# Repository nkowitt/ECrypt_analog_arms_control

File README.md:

# ECrypt_analog_arms_control
Design documentation for the analog information barrier circuit and data described in Warhead Verification with Neutron Beams and an
Analog Information Barrier.

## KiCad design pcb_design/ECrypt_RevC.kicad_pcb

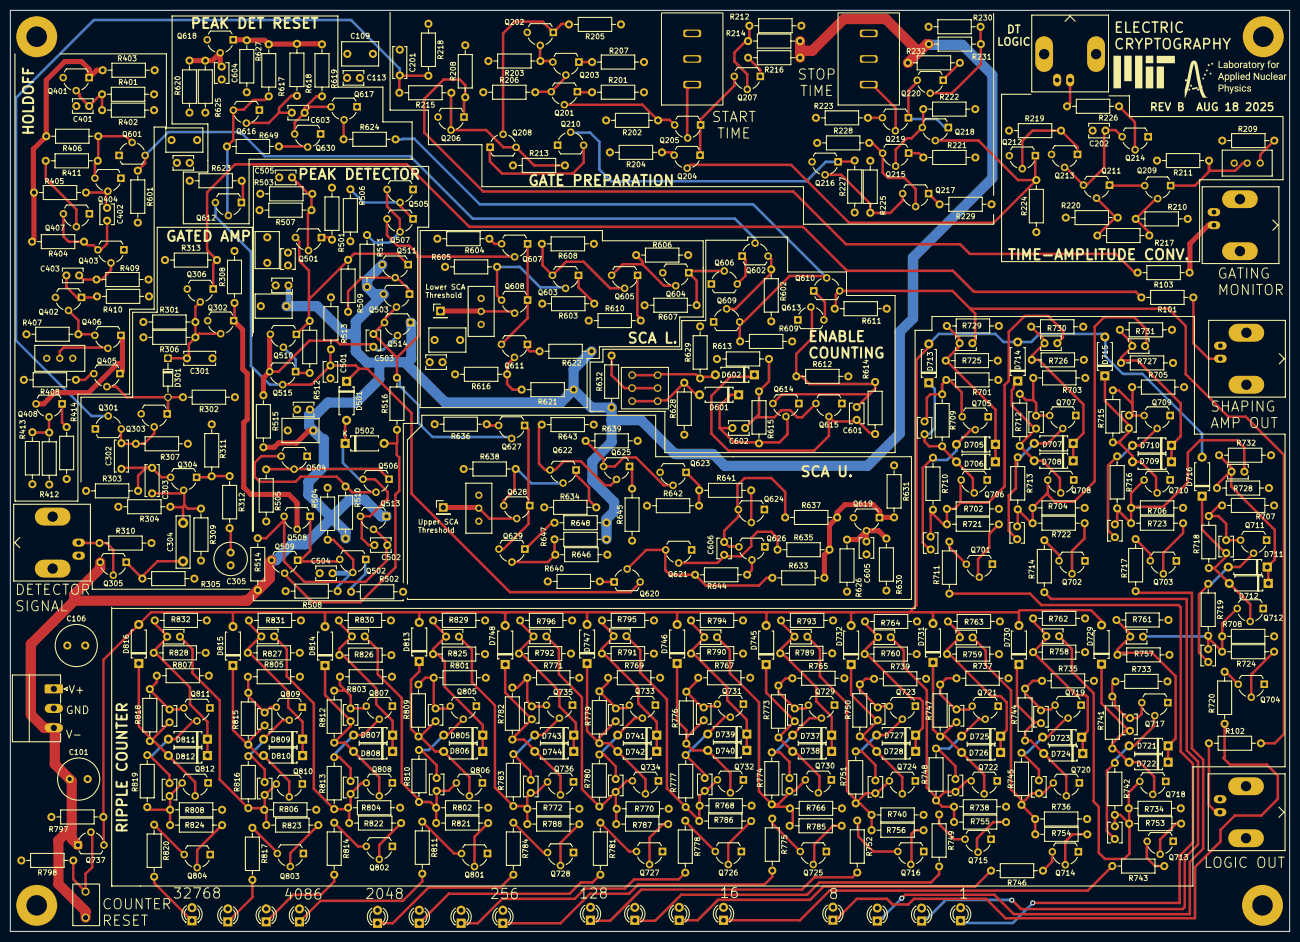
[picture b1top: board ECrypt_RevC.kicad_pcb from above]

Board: 4 copper layers, 250.0 x 180.0 mm, 556 parts (0 on the bottom side), 266 nets.

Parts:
C101, C106: 100u; C_Radial_D8.0mm_H7.0mm_P3.50mm
C102, C103, C107, C108, C109, C110: 100n; C_Rect_L7.0mm_W4.5mm_P5.00mm
C104, C105, C111, C112, C113, C114, C202, C403, C501: 1n; C_Disc_D3.8mm_W2.6mm_P2.50mm
C201: 470p; C_Disc_D6.0mm_W2.5mm_P5.00mm
C301: 100p; C_Disc_D6.0mm_W2.5mm_P5.00mm
C302: 10n; C_Disc_D6.0mm_W2.5mm_P5.00mm
C303: 22p; C_Disc_D6.0mm_W2.5mm_P5.00mm
C304: 1n; C_Rect_L10.0mm_W2.5mm_P7.50mm_MKS4
C305: 1u; C_Radial_D6.3mm_H5.0mm_P2.50mm
C401, C504, C505, C604, C605: 10n; C_Disc_D3.8mm_W2.6mm_P2.50mm
C402, C603: 2.2n; C_Disc_D3.8mm_W2.6mm_P2.50mm
C502: 22p; C_Disc_D3.8mm_W2.6mm_P2.50mm
C503: 100p; C_Disc_D3.8mm_W2.6mm_P2.50mm
C601, C602, C701, C702, C703, C704, C705, C706, C707, C708, C713, C714, C715, C716, C717, C718, C719, C720, C725, C726, C727, C728, C729, C730, C731, C732, C801, C802, C803, C804, C805, C806, C807, C808: 270p; C_Disc_D3.8mm_W2.6mm_P2.50mm
C606: 4.7n; C_Disc_D3.8mm_W2.6mm_P2.50mm
C709, C710, C711, C712, C721, C722, C723, C724, C733, C734, C735, C736, C809, C810, C811, C812: 220p; C_Disc_D3.8mm_W2.6mm_P2.50mm
D301: D; D_DO-34_SOD68_P7.62mm_Horizontal
D501, D502, D601, D602, D705, D706, D707, D708, D709, D710, D711, D712, D713, D714, D715, D716, D721, D722, D723, D724, D725, D726, D727, D728, D729, D730, D731, D732, D737, D738, D739, D740, D741, D742, D743, D744, D745, D746, D747, D748, D805, D806, D807, D808, D809, D810, D811, D812, D813, D814, D815, D816: D; D_A-405_P7.62mm_Horizontal
D701, D702, D703, D704, D717, D718, D719, D720, D733, D734, D735, D736, D801, D802, D803, D804: LED; LED_D3.0mm
H101, H102, H103, H104: MountingHole_Pad; MountingHole_4mm_Pad
J101: Conn_01x03_Pin; PhoenixContact_MC_1,5_3-G-3.81_1x03_P3.81mm_Horizontal
J102, J103, J104, J105, J106: Conn_Coaxial; BNC_Amphenol_B6252HB-NPP3G-50_Horizontal
Q201, Q206, Q209, Q211, Q213, Q215, Q303, Q305, Q501, Q502, Q503, Q504, Q505, Q506, Q507, Q508, Q509, Q510, Q511, Q515, Q603, Q622: 2N3906; TO-92L_Wide
Q202, Q203, Q204, Q205, Q207, Q212, Q214, Q216, Q217, Q218, Q219, Q220, Q302, Q304, Q306, Q401, Q402, Q403, Q404, Q405, Q406, Q407, Q408, Q513, Q514, Q604, Q605, Q607, Q608, Q611, Q614, Q615, Q616, Q617, Q618, Q619, Q621, Q623, Q624, Q625, Q626, Q627, Q628, Q629, Q630, Q701, Q702, Q703, Q704, Q705, Q706, Q707, Q708, Q709, Q710, Q711, Q712, Q713, Q714, Q715, Q716, Q717, Q718, Q719, Q720, Q721, Q722, Q723, Q724, Q725, Q726, Q727, Q728, Q729, Q730, Q731, Q732, Q733, Q734, Q735, Q736, Q801, Q802, Q803, Q804, Q805, Q806, Q807, Q808, Q809, Q810, Q811, Q812: 2N3904; TO-92L_Wide
Q208, Q210, Q301, Q601, Q602, Q606, Q609, Q610, Q612, Q613, Q620, Q737: 2N7000; TO-92L_Wide
R101, R102, R103, R310, R505, R506: 50; R_Axial_DIN0207_L6.3mm_D2.5mm_P10.16mm_Horizontal
R201, R202, R204, R205, R207, R208, R209, R211, R213, R215, R216, R218, R221, R222, R223, R226, R227, R229, R232, R303, R401, R402, R403, R404, R406, R409, R414, R501, R502, R503, R504, R601, R602, R603, R607, R609, R610, R611, R612, R613, R617, R618, R619, R620, R622, R624, R625, R627, R633, R634, R637, R642, R645, R648, R701, R702, R703, R704, R705, R706, R707, R708, R711, R714, R717, R720, R733, R734, R735, R736, R737, R738, R739, R740, R743, R746, R749, R752, R765, R766, R767, R768, R769, R770, R771, R772, R775, R778, R781, R784, R801, R802, R803, R804, R805, R806, R807, R808, R811, R814, R817, R820: 1k; R_Axial_DIN0207_L6.3mm_D2.5mm_P10.16mm_Horizontal
R203, R225, R606, R608, R639, R643: 15k; R_Axial_DIN0207_L6.3mm_D2.5mm_P10.16mm_Horizontal
R206, R228: 5k; R_Axial_DIN0207_L6.3mm_D2.5mm_P10.16mm_Horizontal
R210, R311: 100; R_Axial_DIN0207_L6.3mm_D2.5mm_P10.16mm_Horizontal
R212, R219, R224, R230, R305, R307, R412, R604, R605, R616, R628, R629, R632, R635, R636, R638, R641, R646, R725, R726, R727, R728, R729, R730, R731, R732, R757, R758, R759, R760, R761, R762, R763, R764, R789, R790, R791, R792, R793, R794, R795, R796, R797, R798, R825, R826, R827, R828, R829, R830, R831, R832: 10k; R_Axial_DIN0207_L6.3mm_D2.5mm_P10.16mm_Horizontal
R214, R231, R413, R621, R647: 900; R_Axial_DIN0207_L6.3mm_D2.5mm_P10.16mm_Horizontal
R217: 75; R_Axial_DIN0207_L6.3mm_D2.5mm_P10.16mm_Horizontal
R220: 910; R_Axial_DIN0207_L6.3mm_D2.5mm_P10.16mm_Horizontal
R301: 2Meg; R_Axial_DIN0207_L6.3mm_D2.5mm_P10.16mm_Horizontal
R302: 1.5k; R_Axial_DIN0207_L6.3mm_D2.5mm_P10.16mm_Horizontal
R304: 3.9k; R_Axial_DIN0207_L6.3mm_D2.5mm_P10.16mm_Horizontal
R306, R614, R615, R709, R710, R712, R713, R715, R716, R718, R719, R741, R742, R744, R745, R747, R748, R750, R751, R773, R774, R776, R777, R779, R780, R782, R783, R809, R810, R812, R813, R815, R816, R818, R819: 100k; R_Axial_DIN0207_L6.3mm_D2.5mm_P10.16mm_Horizontal
R308, R313, R721, R722, R723, R724, R753, R754, R755, R756, R785, R786, R787, R788, R821, R822, R823, R824: 40k; R_Axial_DIN0207_L6.3mm_D2.5mm_P10.16mm_Horizontal
R309: 600; R_Axial_DIN0207_L6.3mm_D2.5mm_P10.16mm_Horizontal
R312: 10; R_Axial_DIN0207_L6.3mm_D2.5mm_P10.16mm_Horizontal
R405, R407, R408, R626, R630, R631: 5.6k; R_Axial_DIN0207_L6.3mm_D2.5mm_P10.16mm_Horizontal
R410, R514, R515: 2.2k; R_Axial_DIN0207_L6.3mm_D2.5mm_P10.16mm_Horizontal
R411, R649: 20k; R_Axial_DIN0207_L6.3mm_D2.5mm_P10.16mm_Horizontal
R507, R508: 11k; R_Axial_DIN0207_L6.3mm_D2.5mm_P10.16mm_Horizontal
R509, R510, R511, R512, R516, R644: 22k; R_Axial_DIN0207_L6.3mm_D2.5mm_P10.16mm_Horizontal
R513: 1Meg; R_Axial_DIN0207_L6.3mm_D2.5mm_P10.16mm_Horizontal
R623, R640: 20; R_Axial_DIN0207_L6.3mm_D2.5mm_P10.16mm_Horizontal
RV201, RV203: R_Potentiometer; Bourns 3590s
RV202, RV401, RV601, RV602: R_Potentiometer_Trim; Potentiometer_Bourns_3296W_Vertical
SW601: SW_Push_DPDT; SW_CK_JS202011CQN_DPDT_Straight
SW701: SW_SPST; SW_DIP_SPSTx01_Piano_10.8x4.1mm_W7.62mm_P2.54mm
TP601: TestPoint; PinHeader_1x01_P2.54mm_Vertical
Upper threshold: TestPoint; PinHeader_1x01_P2.54mm_Vertical

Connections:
+VDC: C106.1, C107.1, C108.1, C109.1, C110.1, C111.1, C112.1, C113.1, C114.1, D701.2 (A), D702.2 (A), D703.2 (A), D704.2 (A), D717.2 (A), D718.2 (A), D719.2 (A), D720.2 (A), D733.2 (A), D734.2 (A), D735.2 (A), D736.2 (A), D801.2 (A), D802.2 (A), D803.2 (A), D804.2 (A), J101.1, Q202.3 (C), Q212.3 (C), Q216.3 (C), Q302.3 (C), Q306.3 (C), Q401.3 (C), Q402.3 (C), Q504.1 (E), Q505.1 (E), Q604.3 (C), Q618.3 (C), Q619.3 (C), Q623.3 (C), R201.2, R202.2, R203.2, R204.2, R208.2, R209.2, R210.2, R211.2, R212.2, R213.1, R219.2, R221.2, R222.2, R223.2, R225.2, R230.2, R301.1, R302.1, R303.1, R304.1, R305.1, R401.2, R407.2, R408.2, R412.2, R501.1, R502.1, R503.1, R504.1, R505.1, R506.1, R601.2, R602.2, R603.2, R604.2, R605.2, R606.2, R609.2, R611.2, R612.2, R613.2, R616.2, R620.2, R626.2, R628.1, R629.2, R634.2, R636.2, R638.2, R639.2, R646.2, R701.2, R702.2, R703.2, R704.2, R705.2, R706.2, R707.2, R708.2, R725.2, R726.2, R727.2, R728.2, R733.2, R734.2, R735.2, R736.2, R737.2, R738.2, R739.2, R740.2, R757.2, R758.2, R759.2, R760.2, R765.2, R766.2, R767.2, R768.2, R769.2, R770.2, R771.2, R772.2, R789.2, R790.2, R791.2, R792.2, R797.2, R798.2, R801.2, R802.2, R803.2, R804.2, R805.2, R806.2, R807.2, R808.2, R825.2, R826.2, R827.2, R828.2, RV201.1, RV203.1, RV401.1, RV601.1, RV602.1
-VDC: C101.1, C102.1, C103.1, C104.1, C105.1, J101.3, Q305.3 (C), Q503.3 (C), Q509.3 (C), Q511.3 (C), Q513.1 (E), Q514.1 (E), Q737.1 (S), R214.1, R216.1, R231.1, R232.1, R510.2, R511.2, R514.2, R515.2, R621.1, R622.1, R632.1, R647.1, R648.1, SW701.1 (A)
DT_Reset: J103.1 (In), R226.1
Detector Signal: J105.1 (In), Q305.2 (B), R310.1
GND_ref: C101.2, C102.2, C103.2, C104.2, C105.2, C106.2, C107.2, C108.2, C109.2, C110.2, C111.2, C112.2, C113.2, C114.2, C201.1, C202.2, C301.1, C305.1, C401.2, C501.2, C504.2, C505.2, C604.2, C605.2, H101.1, H102.1, H103.1, H104.1, J101.2, J102.2 (Ext), J103.2 (Ext), J104.2 (Ext), J105.2 (Ext), J106.2 (Ext), Q206.3 (C), Q210.1 (S), Q213.3 (C), Q214.1 (E), Q301.1 (S), Q303.3 (C), Q403.1 (E), Q404.1 (E), Q407.1 (E), Q601.1 (S), Q606.1 (S), Q609.1 (S), Q613.1 (S), Q614.1 (E), Q615.1 (E), Q616.1 (E), Q617.1 (E), Q621.1 (E), Q624.1 (E), Q626.1 (E), Q630.1 (E), Q701.1 (E), Q702.1 (E), Q703.1 (E), Q704.1 (E), Q705.1 (E), Q706.1 (E), Q707.1 (E), Q708.1 (E), Q709.1 (E), Q710.1 (E), Q711.1 (E), Q712.1 (E), Q713.1 (E), Q714.1 (E), Q715.1 (E), Q716.1 (E), Q717.1 (E), Q718.1 (E), Q719.1 (E), Q720.1 (E), Q721.1 (E), Q722.1 (E), Q723.1 (E), Q724.1 (E), Q725.1 (E), Q726.1 (E), Q727.1 (E), Q728.1 (E), Q729.1 (E), Q730.1 (E), Q731.1 (E), Q732.1 (E), Q733.1 (E), Q734.1 (E), Q735.1 (E), Q736.1 (E), Q801.1 (E), Q802.1 (E), Q803.1 (E), Q804.1 (E), Q805.1 (E), Q806.1 (E), Q807.1 (E), Q808.1 (E), Q809.1 (E), Q810.1 (E), Q811.1 (E), Q812.1 (E), R205.1, R206.1, R207.1, R218.1, R220.1, R224.1, R227.1, R228.1, R229.1, R306.2, R307.2, R308.2, R309.2, R310.2, R311.2, R313.1, R402.1, R403.1, R409.1, R410.1, R413.1, R414.1, R507.2, R508.2, R513.2, R607.1, R608.1, R610.1, R623.1, R625.1, R627.1, R630.1, R631.1, R640.1, R642.1, R643.1, R645.1, R729.1, R730.1, R731.1, R732.1, R761.1, R762.1, R763.1, R764.1, R793.1, R794.1, R795.1, R796.1, R829.1, R830.1, R831.1, R832.1, RV201.3, RV203.3, RV401.3, RV601.3, RV602.3
Gating Monitor: Q206.1 (E), R103.2, R208.1
Gating Signal: C201.2, Q301.2 (G), R215.2, R218.2
Holdoff: Q404.3 (C), Q601.2 (G), R406.1, R411.1
unnamed: C305.2, R312.2
unnamed: C301.2, D301.1 (K), Q302.2 (B), Q306.2 (B), R301.2, R306.1
unnamed: C502.1, D501.2 (A), D502.1 (K), Q506.3 (C), Q513.3 (C)
unnamed: D502.2 (A), Q509.2 (B), R516.1
unnamed: D601.2 (A), R628.2, SW601.1 (A), SW601.4 (A)
unnamed: C602.2, D601.1 (K), Q614.2 (B), R615.1
unnamed: D602.2 (A), R629.1, SW601.3 (C), SW601.6 (C)
unnamed: C601.1, D602.1 (K), Q615.2 (B), R614.2
unnamed: D701.1 (K), R711.2
unnamed: D702.1 (K), R714.2
unnamed: D703.1 (K), R717.2
unnamed: D704.1 (K), R720.2
unnamed: C702.2, D705.2 (A), Q705.2 (B), R710.1
unnamed: C709.2, D705.1 (K), D706.1 (K), R725.1, R729.2
unnamed: C701.1, D706.2 (A), D713.1 (K), Q706.2 (B), R709.2
unnamed: C704.2, D707.2 (A), Q707.2 (B), R713.1
unnamed: C710.2, D707.1 (K), D708.1 (K), R726.1, R730.2
unnamed: C703.1, D708.2 (A), D714.1 (K), Q708.2 (B), R712.2
unnamed: C706.2, D709.2 (A), Q709.2 (B), R716.1
unnamed: C711.2, D709.1 (K), D710.1 (K), R727.1, R731.2
unnamed: C705.1, D710.2 (A), D715.1 (K), Q710.2 (B), R715.2
unnamed: C708.2, D711.2 (A), Q711.2 (B), R719.1
unnamed: C712.2, D711.1 (K), D712.1 (K), R728.1, R732.2
unnamed: C707.1, D712.2 (A), D716.1 (K), Q712.2 (B), R718.2
unnamed: D717.1 (K), R743.2
unnamed: D718.1 (K), R746.2
unnamed: D719.1 (K), R749.2
unnamed: D720.1 (K), R752.2
unnamed: C714.2, D721.2 (A), Q717.2 (B), R742.1
unnamed: C721.2, D721.1 (K), D722.1 (K), R757.1, R761.2
unnamed: C713.1, D722.2 (A), D729.1 (K), Q718.2 (B), R741.2
unnamed: C716.2, D723.2 (A), Q719.2 (B), R745.1
unnamed: C722.2, D723.1 (K), D724.1 (K), R758.1, R762.2
unnamed: C715.1, D724.2 (A), D730.1 (K), Q720.2 (B), R744.2
unnamed: C718.2, D725.2 (A), Q721.2 (B), R748.1
unnamed: C723.2, D725.1 (K), D726.1 (K), R759.1, R763.2
unnamed: C717.1, D726.2 (A), D731.1 (K), Q722.2 (B), R747.2
unnamed: C720.2, D727.2 (A), Q723.2 (B), R751.1
unnamed: C724.2, D727.1 (K), D728.1 (K), R760.1, R764.2
unnamed: C719.1, D728.2 (A), D732.1 (K), Q724.2 (B), R750.2
unnamed: D733.1 (K), R775.2
unnamed: D734.1 (K), R778.2
unnamed: D735.1 (K), R781.2
unnamed: D736.1 (K), R784.2
unnamed: C726.2, D737.2 (A), Q729.2 (B), R774.1
unnamed: C733.2, D737.1 (K), D738.1 (K), R789.1, R793.2
unnamed: C725.1, D738.2 (A), D745.1 (K), Q730.2 (B), R773.2
unnamed: C728.2, D739.2 (A), Q731.2 (B), R777.1
unnamed: C734.2, D739.1 (K), D740.1 (K), R790.1, R794.2
unnamed: C727.1, D740.2 (A), D746.1 (K), Q732.2 (B), R776.2
unnamed: C730.2, D741.2 (A), Q733.2 (B), R780.1
unnamed: C735.2, D741.1 (K), D742.1 (K), R791.1, R795.2
unnamed: C729.1, D742.2 (A), D747.1 (K), Q734.2 (B), R779.2
unnamed: C732.2, D743.2 (A), Q735.2 (B), R783.1
unnamed: C736.2, D743.1 (K), D744.1 (K), R792.1, R796.2
unnamed: C731.1, D744.2 (A), D748.1 (K), Q736.2 (B), R782.2
unnamed: D801.1 (K), R811.2
unnamed: D802.1 (K), R814.2
unnamed: D803.1 (K), R817.2
unnamed: D804.1 (K), R820.2
unnamed: C802.2, D805.2 (A), Q805.2 (B), R810.1
unnamed: C809.2, D805.1 (K), D806.1 (K), R825.1, R829.2
unnamed: C801.1, D806.2 (A), D813.1 (K), Q806.2 (B), R809.2
unnamed: C804.2, D807.2 (A), Q807.2 (B), R813.1
unnamed: C810.2, D807.1 (K), D808.1 (K), R826.1, R830.2
unnamed: C803.1, D808.2 (A), D814.1 (K), Q808.2 (B), R812.2
unnamed: C806.2, D809.2 (A), Q809.2 (B), R816.1
unnamed: C811.2, D809.1 (K), D810.1 (K), R827.1, R831.2
unnamed: C805.1, D810.2 (A), D815.1 (K), Q810.2 (B), R815.2
unnamed: C808.2, D811.2 (A), Q811.2 (B), R819.1
unnamed: C812.2, D811.1 (K), D812.1 (K), R828.1, R832.2
unnamed: C807.1, D812.2 (A), D816.1 (K), Q812.2 (B), R818.2
unnamed: J102.1 (In), R101.1
unnamed: J104.1 (In), R102.1
unnamed: J106.1 (In), R103.1
unnamed: Q201.2 (B), Q205.3 (C), R202.1
unnamed: Q201.3 (C), Q203.2 (B), R206.2
unnamed: Q201.1 (E), R201.1
unnamed: Q202.2 (B), Q203.3 (C), R203.1
unnamed: Q202.1 (E), Q208.2 (G), R205.2
unnamed: Q203.1 (E), R207.2
unnamed: Q204.2 (B), Q212.1 (E), Q218.2 (B), R224.2
unnamed: Q204.3 (C), R204.1
unnamed: Q204.1 (E), Q205.1 (E), Q207.3 (C)
unnamed: Q205.2 (B), RV201.2
unnamed: Q206.2 (B), Q208.3 (D), R213.2, R215.1
unnamed: Q207.2 (B), R212.1, R214.2
unnamed: Q207.1 (E), R216.2
unnamed: Q208.1 (S), Q210.3 (D)
unnamed: Q209.2 (B), R210.1, R217.2
unnamed: Q209.3 (C), Q211.1 (E)
unnamed: Q209.1 (E), R211.1, RV202.2
unnamed: Q210.2 (G), Q216.1 (E), R227.2
unnamed: Q211.2 (B), R217.1, R220.2
unnamed: C202.1, Q211.3 (C), Q213.2 (B), Q214.3 (C)
unnamed: Q212.2 (B), Q213.1 (E), R219.1
unnamed: Q214.2 (B), R226.2
unnamed: Q215.2 (B), Q218.3 (C), R222.1
unnamed: Q215.3 (C), Q217.2 (B), R228.2
unnamed: Q215.1 (E), R221.1
unnamed: Q216.2 (B), Q217.3 (C), R225.1
unnamed: Q217.1 (E), R229.2
unnamed: Q218.1 (E), Q219.1 (E), Q220.3 (C)
unnamed: Q219.2 (B), RV203.2
unnamed: Q219.3 (C), R223.1
unnamed: Q220.2 (B), R230.1, R231.2
unnamed: Q220.1 (E), R232.2
unnamed: C302.2, Q301.3 (D), Q303.2 (B), R307.1
unnamed: C303.1, C304.2, Q304.2 (B), R304.2, R309.1
unnamed: C302.1, C303.2, Q304.3 (C), R303.2
unnamed: Q304.1 (E), R311.1, R312.1
unnamed: C304.1, Q305.1 (E), R305.2
unnamed: C401.1, Q401.2 (B), R401.1, R402.2
unnamed: Q401.1 (E), R403.2, R404.2, R405.2, R406.2
unnamed: Q402.2 (B), Q406.3 (C), R407.1
unnamed: C403.2, Q402.1 (E), R410.2
unnamed: C403.1, Q403.2 (B), R409.2
unnamed: C402.2, Q403.3 (C), Q407.3 (C), R404.1
unnamed: C402.1, Q404.2 (B), R405.1
unnamed: Q405.3 (C), R408.1
unnamed: Q405.1 (E), Q406.1 (E), Q408.3 (C)
unnamed: Q406.2 (B), RV401.2
unnamed: Q407.2 (B), R411.2
unnamed: Q408.2 (B), R412.1, R413.2
unnamed: Q408.1 (E), R414.2
unnamed: C505.1, Q501.2 (B), R503.2, R507.1
unnamed: Q501.3 (C), Q510.1 (E), Q511.1 (E), R509.1, R512.1
unnamed: Q501.1 (E), R501.2
unnamed: C504.1, Q502.2 (B), R504.2, R508.1
unnamed: Q502.3 (C), Q508.1 (E), Q509.1 (E)
unnamed: Q502.1 (E), R502.2
unnamed: Q503.1 (E), Q511.2 (B), R509.2
unnamed: Q504.2 (B), Q506.1 (E), R505.2
unnamed: Q504.3 (C), Q506.2 (B), R510.1
unnamed: Q505.2 (B), Q507.1 (E), R506.2
unnamed: Q505.3 (C), Q507.2 (B), R511.1
unnamed: C502.2, Q508.3 (C), Q513.2 (B), R514.1
unnamed: Q510.2 (B), Q515.1 (E), R512.2
unnamed: C503.2, Q510.3 (C), Q514.2 (B), Q515.3 (C), R515.1
unnamed: Q601.3 (D), Q602.2 (G), R601.1
unnamed: Q602.3 (D), Q609.2 (G), R602.1
unnamed: Q602.1 (S), Q606.3 (D)
unnamed: Q603.2 (B), Q608.3 (C), R605.1
unnamed: Q603.3 (C), Q605.2 (B), R608.2
unnamed: Q603.1 (E), R603.1
unnamed: Q604.2 (B), Q605.3 (C), R606.1
unnamed: Q604.1 (E), Q606.2 (G), R607.2
unnamed: Q605.1 (E), R610.2
unnamed: Q607.3 (C), R604.1
unnamed: Q607.1 (E), Q608.1 (E), Q611.3 (C)
unnamed: Q608.2 (B), RV601.2, TP601.1
unnamed: Q609.3 (D), Q610.2 (G), R609.1, R624.2
unnamed: Q610.1 (S), Q613.3 (D)
unnamed: Q611.2 (B), R616.1, R621.2
unnamed: Q611.1 (E), R622.2
unnamed: Q612.2 (G), Q616.3 (C), R617.1, R649.2
unnamed: Q612.1 (S), R623.2
unnamed: C601.2, Q613.2 (G), Q614.3 (C), R612.1, R614.1
unnamed: C602.1, Q615.3 (C), R613.1, R615.2
unnamed: C603.2, Q616.2 (B), R618.1
unnamed: Q617.2 (B), R624.1
unnamed: C603.1, Q617.3 (C), Q630.3 (C), R619.1
unnamed: C604.1, Q618.2 (B), R620.1, R625.2
unnamed: Q618.1 (E), R617.2, R618.2, R619.2, R627.2
unnamed: C605.1, Q619.2 (B), R626.1, R630.2
unnamed: Q619.1 (E), R631.2, R633.2, R635.2, R637.2
unnamed: Q620.2 (G), Q621.3 (C), R633.1, R644.1
unnamed: Q620.1 (S), R640.2
unnamed: C606.2, Q621.2 (B), R635.1
unnamed: Q622.2 (B), Q628.3 (C), R638.1
unnamed: Q622.3 (C), Q625.2 (B), R643.2
unnamed: Q622.1 (E), R634.1
unnamed: Q623.2 (B), Q625.3 (C), R639.1
unnamed: Q623.1 (E), R641.2, R642.2
unnamed: Q624.2 (B), R641.1
unnamed: C606.1, Q624.3 (C), Q626.3 (C), R637.1
unnamed: Q625.1 (E), R645.2
unnamed: Q626.2 (B), R644.2
unnamed: Q627.3 (C), R636.1
unnamed: Q627.1 (E), Q628.1 (E), Q629.3 (C)
unnamed: Q628.2 (B), RV602.2, Upper threshold.1
unnamed: Q629.2 (B), R646.1, R647.2
unnamed: Q629.1 (E), R648.2
unnamed: Q630.2 (B), R649.1
unnamed: Q701.2 (B), R721.2
unnamed: Q701.3 (C), R711.1
unnamed: Q702.2 (B), R722.2
unnamed: Q702.3 (C), R714.1
unnamed: Q703.2 (B), R723.2
unnamed: Q703.3 (C), R717.1
unnamed: Q704.2 (B), R724.2
unnamed: Q704.3 (C), R720.1
unnamed: C701.2, Q705.3 (C), R701.1, R709.1
unnamed: C702.1, C710.1, Q706.3 (C), R702.1, R710.2, R721.1
unnamed: C703.2, Q707.3 (C), R703.1, R712.1
unnamed: C704.1, C711.1, Q708.3 (C), R704.1, R713.2, R722.1
unnamed: C705.2, Q709.3 (C), R705.1, R715.1
unnamed: C706.1, C712.1, Q710.3 (C), R706.1, R716.2, R723.1
unnamed: C707.2, Q711.3 (C), R707.1, R718.1
unnamed: C708.1, C721.1, Q712.3 (C), R708.1, R719.2, R724.1
unnamed: Q713.2 (B), R753.2
unnamed: Q713.3 (C), R743.1
unnamed: Q714.2 (B), R754.2
unnamed: Q714.3 (C), R746.1
unnamed: Q715.2 (B), R755.2
unnamed: Q715.3 (C), R749.1
unnamed: Q716.2 (B), R756.2
unnamed: Q716.3 (C), R752.1
unnamed: C713.2, Q717.3 (C), R733.1, R741.1
unnamed: C714.1, C722.1, Q718.3 (C), R734.1, R742.2, R753.1
unnamed: C715.2, Q719.3 (C), R735.1, R744.1
unnamed: C716.1, C723.1, Q720.3 (C), R736.1, R745.2, R754.1
unnamed: C717.2, Q721.3 (C), R737.1, R747.1
unnamed: C718.1, C724.1, Q722.3 (C), R738.1, R748.2, R755.1
unnamed: C719.2, Q723.3 (C), R739.1, R750.1
unnamed: C720.1, C733.1, Q724.3 (C), R740.1, R751.2, R756.1
unnamed: Q725.2 (B), R785.2
unnamed: Q725.3 (C), R775.1
unnamed: Q726.2 (B), R786.2
unnamed: Q726.3 (C), R778.1
unnamed: Q727.2 (B), R787.2
unnamed: Q727.3 (C), R781.1
unnamed: Q728.2 (B), R788.2
unnamed: Q728.3 (C), R784.1
unnamed: C725.2, Q729.3 (C), R765.1, R773.1
unnamed: C726.1, C734.1, Q730.3 (C), R766.1, R774.2, R785.1
unnamed: C727.2, Q731.3 (C), R767.1, R776.1
unnamed: C728.1, C735.1, Q732.3 (C), R768.1, R777.2, R786.1
unnamed: C729.2, Q733.3 (C), R769.1, R779.1
unnamed: C730.1, C736.1, Q734.3 (C), R770.1, R780.2, R787.1
unnamed: C731.2, Q735.3 (C), R771.1, R782.1
unnamed: Q737.2 (G), R798.1, SW701.2 (B)
unnamed: Q801.2 (B), R821.2
unnamed: Q801.3 (C), R811.1
unnamed: Q802.2 (B), R822.2
unnamed: Q802.3 (C), R814.1
unnamed: Q803.2 (B), R823.2
unnamed: Q803.3 (C), R817.1
unnamed: Q804.2 (B), R824.2
unnamed: Q804.3 (C), R820.1
unnamed: C801.2, Q805.3 (C), R801.1, R809.1
unnamed: C802.1, C810.1, Q806.3 (C), R802.1, R810.2, R821.1
unnamed: C803.2, Q807.3 (C), R803.1, R812.1
unnamed: C804.1, C811.1, Q808.3 (C), R804.1, R813.2, R822.1
unnamed: C805.2, Q809.3 (C), R805.1, R815.1
unnamed: C806.1, C812.1, Q810.3 (C), R806.1, R816.2, R823.1
unnamed: C807.2, Q811.3 (C), R807.1, R818.1
unnamed: C808.1, Q812.3 (C), R808.1, R819.2, R824.1
unnamed: R209.1, RV202.1
unnamed: R632.2, SW601.2 (B), SW601.5 (B)
Shapped Signal: Q302.1 (E), Q508.2 (B), R308.1
Trigger Signal: D301.2 (A), Q303.1 (E), Q405.2 (B), R302.2
amp_out: Q306.1 (E), R101.2, R313.2
bit_12: C732.1, C809.1, Q736.3 (C), R772.1, R783.2, R788.1
logic_out: C709.1, Q610.3 (D), R102.2, R611.1
peak_det_cap: C501.1, D501.1 (K), Q515.2 (B), Q612.3 (D), Q620.3 (D), R513.1
peak_det_out: C503.1, Q503.2 (B), Q507.3 (C), Q514.3 (C), Q607.2 (B), Q627.2 (B), R516.2
reset_line: D713.2 (A), D714.2 (A), D715.2 (A), D716.2 (A), D729.2 (A), D730.2 (A), D731.2 (A), D732.2 (A), D745.2 (A), D746.2 (A), D747.2 (A), D748.2 (A), D813.2 (A), D814.2 (A), D815.2 (A), D816.2 (A), Q737.3 (D), R797.1

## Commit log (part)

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2026-04-10 Added pcb and spice simulations
